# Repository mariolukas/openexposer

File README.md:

#Open Exposer

OpenExposer is a low cost open source stereolithography printer.

</img>
</img>

## Hardware

### 3D printed parts
For this early prototype you will need some 3d printed parts. All parts were made with OpenSCAD. They are located in the 3D parts folder.

### Electronics

#### Controller Board
The Open Exposer uses an Arduino UNO. There is no Arduino Shield until now. I am using the FabScan Shield for mounting the motor drivers until now. 

#### Polygon Mirror
Currently Open Exposer uses a Aficio 1018 G029-1961 (or compatibel with a NBC3111 driver ic) Polygon Mirror. It can be ordered from Aliexpress or Ebay. 
http://www.aliexpress.com/snapshot/303668242.html?orderId=60566587991552

#####Pinout: 

*	pin1: clock
*	Pin2: No connection.
*	pin3: Motor start/ stop: Gnd is start +5
*	Pin4: Motor Ground.
*	Pin5: Vmotor: 12V

For generating the clock signal, a attiny2313 is used. It will be replaced by a 555 soon.

#### Laser Driver
The laser unit uses a TTL laser driver. The laser driver Board is located in the electronics folder. It is based on the di4drive TTL laser driver.

## Software

### Slicing
In Software/Tools you will find grslicer. Which is able to slice STL files to open exposer G-Code. You can use g-code viewer check the results.
There is a folder test Pattern which generates a test pattern g-code. This g-code can be uses for example for a calibration process.

### Host
The host application is a small python script which sends the g-code files line by line to the Open Exposer

### Firmware
Open Exposer Arduino Firmware. 

##Other use cases

* uv PCB exposing

##We will keep you informed
*	<a href="http://twitter.com/l_k3">Twitter</a>
*	<a href="https://www.youtube.com/user/clustermaster23">Youtube</a>
*	<a href="http://www.mariolukas.de/?s=openexposer">Blog</a>
*	<a href="https://hackaday.io/project/1129-openexposer">hackday.io (Hackaday Prize Project 2014)</a>

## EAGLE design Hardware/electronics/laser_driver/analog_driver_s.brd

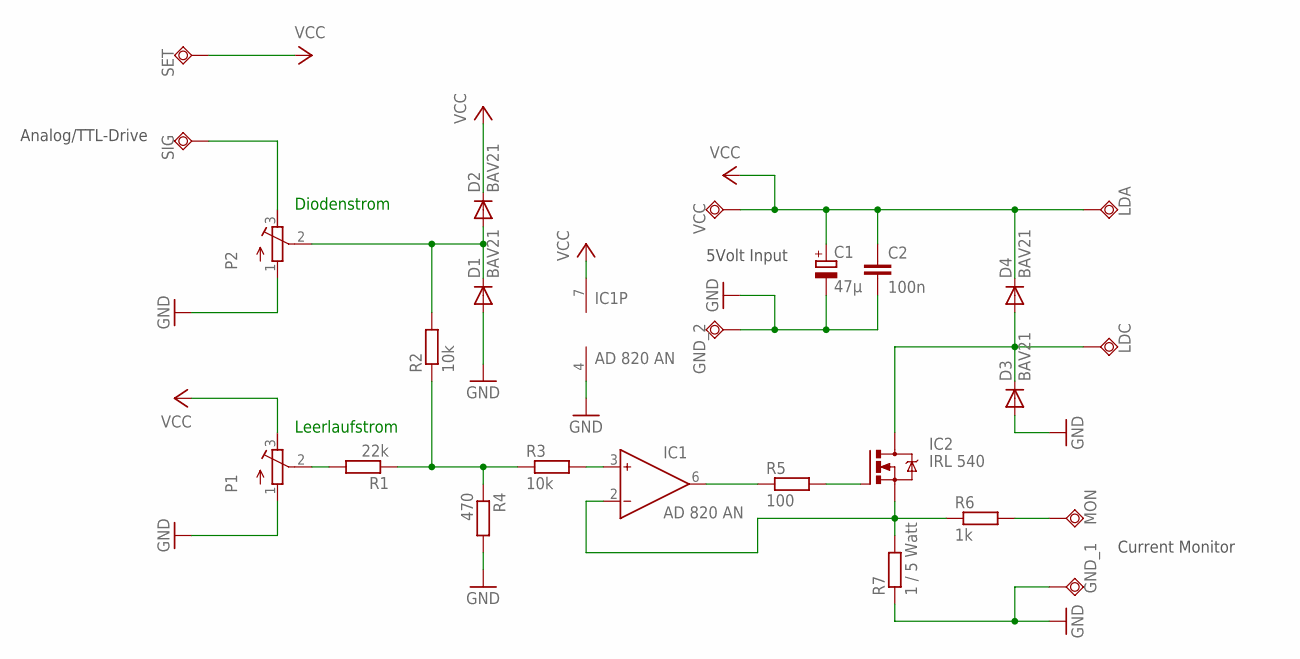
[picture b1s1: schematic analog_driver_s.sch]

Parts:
C1: 47µ; E2-5
C2: 100n; C025-024X044
D1, D2, D3, D4: BAV21; DO35-10
GND_1, GND_2: PAD
IC1: AD 820 AN; DIL08
IC2: IRL 540; TO220BV
LDA: PAD
LDC: PAD
MON: PAD
P1, P2: R-TRIMM3296W; RTRIM3296W
R1: 22k; 0309V
R2: 10k; 0309V
R3: 10k; 0309/10
R4: 470; 0309V
R5: 100; 0309V
R6: 1k; 0309V
R7: 1 / 5 Watt; 0617V
SET: PAD
SIG: PAD
VCC: PAD

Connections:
GND: C1.-, C2.2, D1.A, D3.A, GND_1.P$1, GND_2.P$1, IC1.4 (V-), P1.1 (E), P2.1 (E), R4.2, R7.1
unnamed: P2.3 (A), SIG.P$1
unnamed: P1.2 (S), R1.2
unnamed: R1.1, R2.1, R3.1, R4.1
unnamed: D1.C, D2.A, P2.2 (S), R2.2
unnamed: IC1.3 (IN+), R3.2
unnamed: IC1.6 (OUT), R5.1
unnamed: IC1.2 (IN-), IC2.S, R6.1, R7.2
unnamed: IC2.G, R5.2
unnamed: MON.P$1, R6.2
unnamed: D3.C, D4.A, IC2.D, LDC.P$1
VCC: C1.+, C2.1, D2.C, D4.C, IC1.7 (V+), LDA.P$1, P1.3 (A), SET.P$1, VCC.P$1

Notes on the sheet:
5Volt Input
Current Monitor
Analog/TTL-Drive
Diodenstrom
Leerlaufstrom

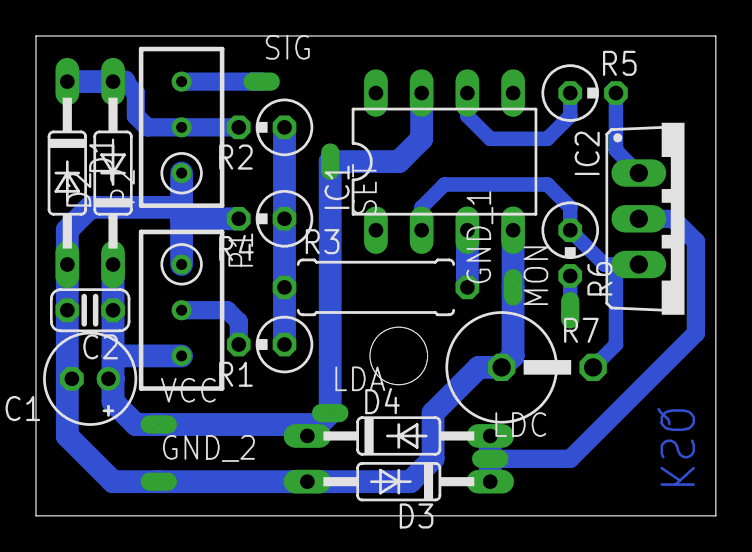
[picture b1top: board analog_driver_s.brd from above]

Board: 2 copper layers, 37.8 x 26.7 mm, 25 parts (0 on the bottom side), 12 nets.

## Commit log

2014-03-19 Initial
2014-03-19 Removed StepperDriver Library
2014-04-18 Added StepperControland ProcessCommand Files
2014-04-18 Added Endstop functions
2014-04-19 refactored main program
2014-04-19 cleaned code and added endstop and axis homing functions
2014-04-19 deleted old files
2014-04-19 - added homeing y axis to setup
2014-04-19 - added z endstop - added speed and acceleration values to config - added new function moveToNextLayer
2014-04-19 - fixed serial event loop - added command parser - refactored process data main loop
2014-04-19 - added function for toggeling direction
2014-04-19 - added host software
2014-04-19 - removed compiled files
2014-05-05 - cleaned folder structure
2014-05-05 -changed folder structure
2014-05-05 - added openscad file for exposer unit
2014-05-05 - added laser driver eagle files and pdf
2014-05-05 - removed files which are not needed
2014-05-05 - cleaned scad code
2014-05-05 - changed Readme.md - added new features to Firmware
2014-05-05 - changed Readme.md
2014-05-05 - added information to Readme.md
2014-05-05 - changed on Readme.md
2014-05-05 - added new command to Firmware
2014-05-05 - added motor enable/disable function
2014-05-05 - added new function for end position of z - refactored/renamed loadfile function - changed resolution values
2014-05-05 - added stl files
2015-04-09 Create gh-pages branch via GitHub
2015-04-22 updated to new open exposer version
2015-04-22 removed some files
2015-04-22 .DS_Store banished!
2015-04-22 added smaller images
2015-04-22 changed Readme.md
2015-04-22 removed .DS_Store files
2015-04-23 - changed README.md - removed some files
2015-04-23 - changed README.md format
2015-11-29 - added variables to show only specific parts of the hardware - allow display assembled as well as only parts
2015-12-29 fixed firmware source
2015-12-31 - added a rudimentary gcode viewer - added a first version of grslicer creating g-code for openexposer - added a python script to generate a test pattern as gcode
2016-01-03 - import facets normals from stl - use 64bit precision for calculations - use center of layer with a little offset for calculating scanlines
2016-01-04 - Fixed import of ascii stl - added octopus example
2016-01-04 - use face vertices y coordinates to filter before intersection
2016-01-04 removed old slicer code
2016-01-04 cleaned repository
2016-01-04 removed image folder
2016-01-04 chaned README.md
2016-01-04 changed README.TXT
2016-01-04 - g-code coordinate system origin now in the center of builing area - some improvements on the gcodeviewer - updated to finer sliced octopus model
2016-02-15 - output settings into gcode
2016-02-15 - added settings to gcode
2016-02-15 - added cmake build scripts for unit tests and arduino sketch - added first unit test dummy
2016-02-16 - moved google test, unit tests and arduino toolchain upwards
2016-02-17 - arduino build script now called by parent build
2016-02-24 - added some fake headers and symbols for compilation of firmware with unit tests - ignore clion ide files - removed ServoTimer2 library
2016-02-24 - laser timings now adaptable with some variables
2016-02-25 - add G06 D0 to finish line
2016-02-25 - Use exposing cycles from gcode to determine end of exposing process for each line - removed function set_exposing_cycles (already given as parameter to expose_line()) - renamed some variables - ref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
2016-02-25 - Replaced define constants for laser state with new enum class LaserState
2016-02-25 - added field to store the length of the buffer to laser_buffer_type - removed laser_data_position
2016-02-25 - added assertion to check maximum length of laser_buffer
2016-02-25 - removed unused variable offset
2016-02-25 - removed unnecessary includes
2016-02-25 - removed no longer needed header file stubs
2016-02-29 - added -std=c++11 as compiler flag - search for arduino sdk in home directory of current user
2016-03-05 - documented cmake build - added feature to use arduino sdk path from environment variable - hex file now created in build directory
2016-03-05 - added troubleshooting if arduino sdk has not been found
2016-03-05 - added example how to set environment variable
2016-03-05 - fixed warnings
2016-03-06 - added license GPLv3
2016-03-06 - moved bitbanging of registers to inline functions of a LaserTimer class - added integration tests for LaserTimer
2016-04-10 Better use EAGLE v7 please ;)
2016-05-03 - added firmware for motor controller
2016-05-03 - new version
2016-05-08 modified polygon motor driver, increased duty cycle
2016-05-16 - added first version firmware working with example gcode "octopus"
